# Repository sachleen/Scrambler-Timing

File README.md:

Scrambler-Timing
================

Laser timing device for the Scrambler event in Science Olympiad

The photogate system uses two lasers and two sensors. When the scrambler passes through the start sensor, it begins timing. When the scrambler passes through the finish sensor, it sends a signal to the start sensor to stop timing.

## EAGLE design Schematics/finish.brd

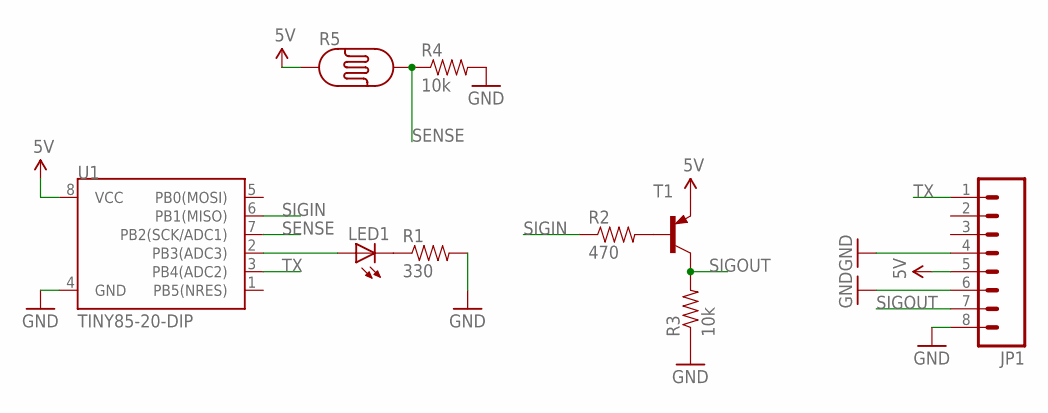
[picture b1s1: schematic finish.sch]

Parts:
JP1: M081X08; 1X08
LED1: LED5MM
R1: 330; AXIAL-0.4
R2: 470; AXIAL-0.4
R3, R4: 10k; AXIAL-0.4
R5: PHOTOCELLPTH; PHOTOCELL
T1: 2N3906-PNP-TO92-EBC; TO92-EBC
U1: TINY85-20-DIP; DIP08

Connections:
5V: JP1.5, R5.1, T1.E, U1.8 (VCC)
GND: JP1.4, JP1.6, JP1.8, R1.P$2 (2), R3.P$1 (1), R4.P$2 (2), U1.4 (GND)
unnamed: LED1.K (C), R1.P$1 (1)
unnamed: LED1.A, U1.2 (PB3(ADC3))
unnamed: R2.P$2 (2), T1.B
SENSE: R4.P$1 (1), R5.2, U1.7 (PB2(SCK/ADC1))
SIGIN: R2.P$1 (1), U1.6 (PB1(MISO))
SIGOUT: JP1.7, R3.P$2 (2), T1.C
TX: JP1.1, U1.3 (PB4(ADC2))

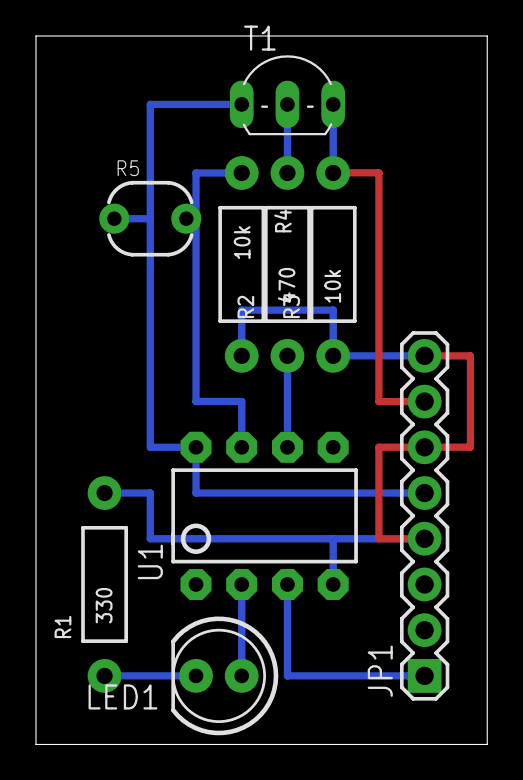
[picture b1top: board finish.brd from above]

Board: 2 copper layers, 25.1 x 39.4 mm, 9 parts (0 on the bottom side), 9 nets.

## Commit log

2014-03-01 Initial Commit.
2014-03-01 Added project description.
2014-03-02 Created start sensor schematic.
2014-03-02 Initial commit of start sensor schematic.
2014-03-02 routed finish sensor
2014-03-03 changed some text sent to serial
2014-03-09 lowered threshold value so time triggers faster

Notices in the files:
parts and their libraries:
SparkFun-DigitalIC: Licensing: CC v3.0 Share-Alike You are welcome to use this library for commercial purposes.
